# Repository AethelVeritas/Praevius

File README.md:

# Praevius
Low profile split wireless keyboard, with a touchpad.

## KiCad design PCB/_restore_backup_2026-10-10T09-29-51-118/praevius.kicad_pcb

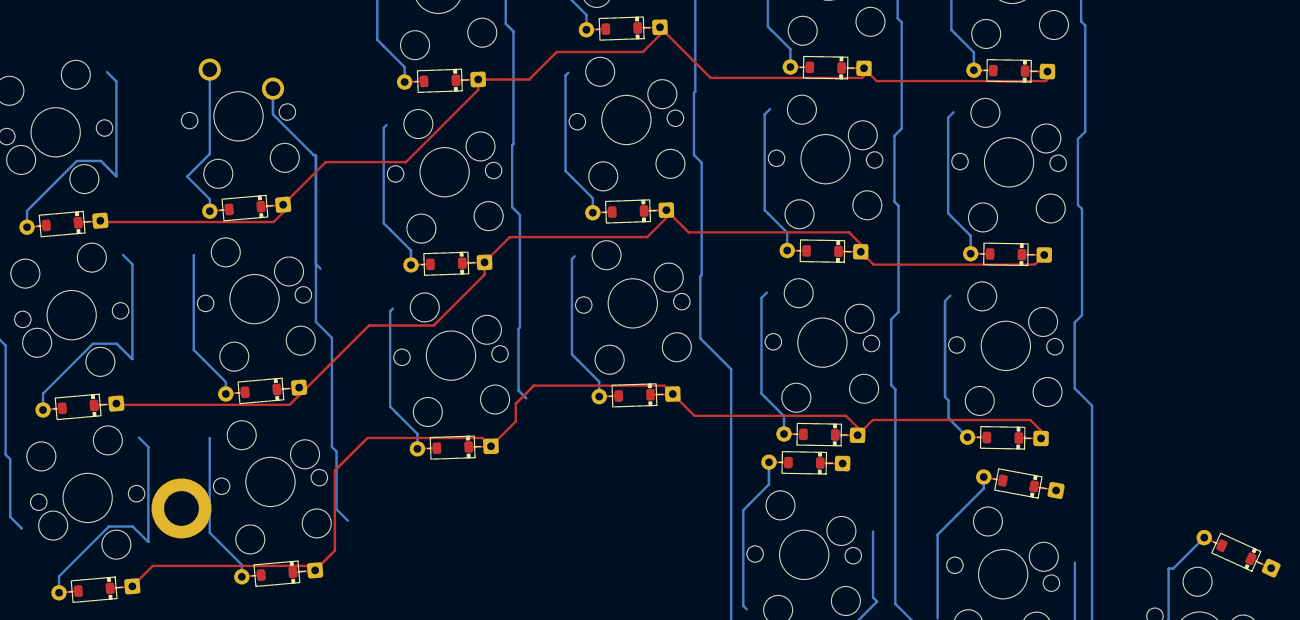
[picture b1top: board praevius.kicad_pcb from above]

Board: 2 copper layers, 42 parts (0 on the bottom side), 31 nets.

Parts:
D1, D2, D3, D4, D5, D6, D7, D8, D9, D10, D11, D12, D13, D14, D15, D16, D17, D18, D19, D20, D21: 1N4149; DO-35_and_SOD-123
SW1, SW3, SW4, SW5, SW6, SW7, SW8, SW9, SW10, SW11, SW12, SW13, SW14, SW15, SW16, SW17, SW18, SW19, SW20, SW21: S; Gateron-KS33+MX-Hotswap-1U
SW2: S; Gateron-KS33-Hotswap+MX_Solderable_1U

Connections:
/LCol0: SW1.1, SW7.1, SW13.1
/LCol1: SW2.1, SW8.1, SW14.1
/LCol2: SW3.1, SW9.1, SW15.1
/LCol3: SW4.1, SW10.1, SW16.1, SW19.1
/LCol4: SW5.1, SW11.1, SW17.1, SW20.1
/LCol5: SW6.1, SW12.1, SW18.1, SW21.1
/LRow0: D1.1 (K), D2.1 (K), D3.1 (K), D4.1 (K), D5.1 (K), D6.1 (K)
/LRow1: D7.1 (K), D8.1 (K), D9.1 (K), D10.1 (K), D11.1 (K), D12.1 (K)
/LRow2: D13.1 (K), D14.1 (K), D15.1 (K), D16.1 (K), D17.1 (K), D18.1 (K)
/LRow3: D19.1 (K), D20.1 (K), D21.1 (K)
unnamed: D1.2 (A), SW1.2
unnamed: D2.2 (A), SW2.2
unnamed: D3.2 (A), SW3.2
unnamed: D4.2 (A), SW4.2
unnamed: D5.2 (A), SW5.2
unnamed: D6.2 (A), SW6.2
unnamed: D7.2 (A), SW7.2
unnamed: D8.2 (A), SW8.2
unnamed: D9.2 (A), SW9.2
unnamed: D10.2 (A), SW10.2
unnamed: D11.2 (A), SW11.2
unnamed: D12.2 (A), SW12.2
unnamed: D13.2 (A), SW13.2
unnamed: D14.2 (A), SW14.2
unnamed: D15.2 (A), SW15.2
unnamed: D16.2 (A), SW16.2
unnamed: D17.2 (A), SW17.2
unnamed: D18.2 (A), SW18.2
unnamed: D19.2 (A), SW19.2
unnamed: D20.2 (A), SW20.2
unnamed: D21.2 (A), SW21.2
